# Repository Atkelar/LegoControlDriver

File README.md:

# LegoControlDriver
Lego Control II to Arduino interface code and info.

This is the code related to the video here: https://www.youtube.com/watch?v=ZT2Cm_PV4GQ

There are plenty of comments in the source code, here's a rundown of the projects:

## Lego-Control-II-Driver 
This is the main Arduino Project - i.e. file - for the driver. Single file only so far, but uses the TimerInterrupt library.

## KiCAD
A simple schematic and PCB for interfacing the Arduino pinout with the 20 pin flat cable connector.

## Atkelar.LegoControlII
My C# library to communicate with the Arduino code. Written in .net core 3.1

## Atkelar.LegoPlotter
A C# command line application that wraps the plotter model and can print a simple HPGL file.

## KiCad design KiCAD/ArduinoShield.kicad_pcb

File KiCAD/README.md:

This KiCAD project contains a simple adapter shield PCB.

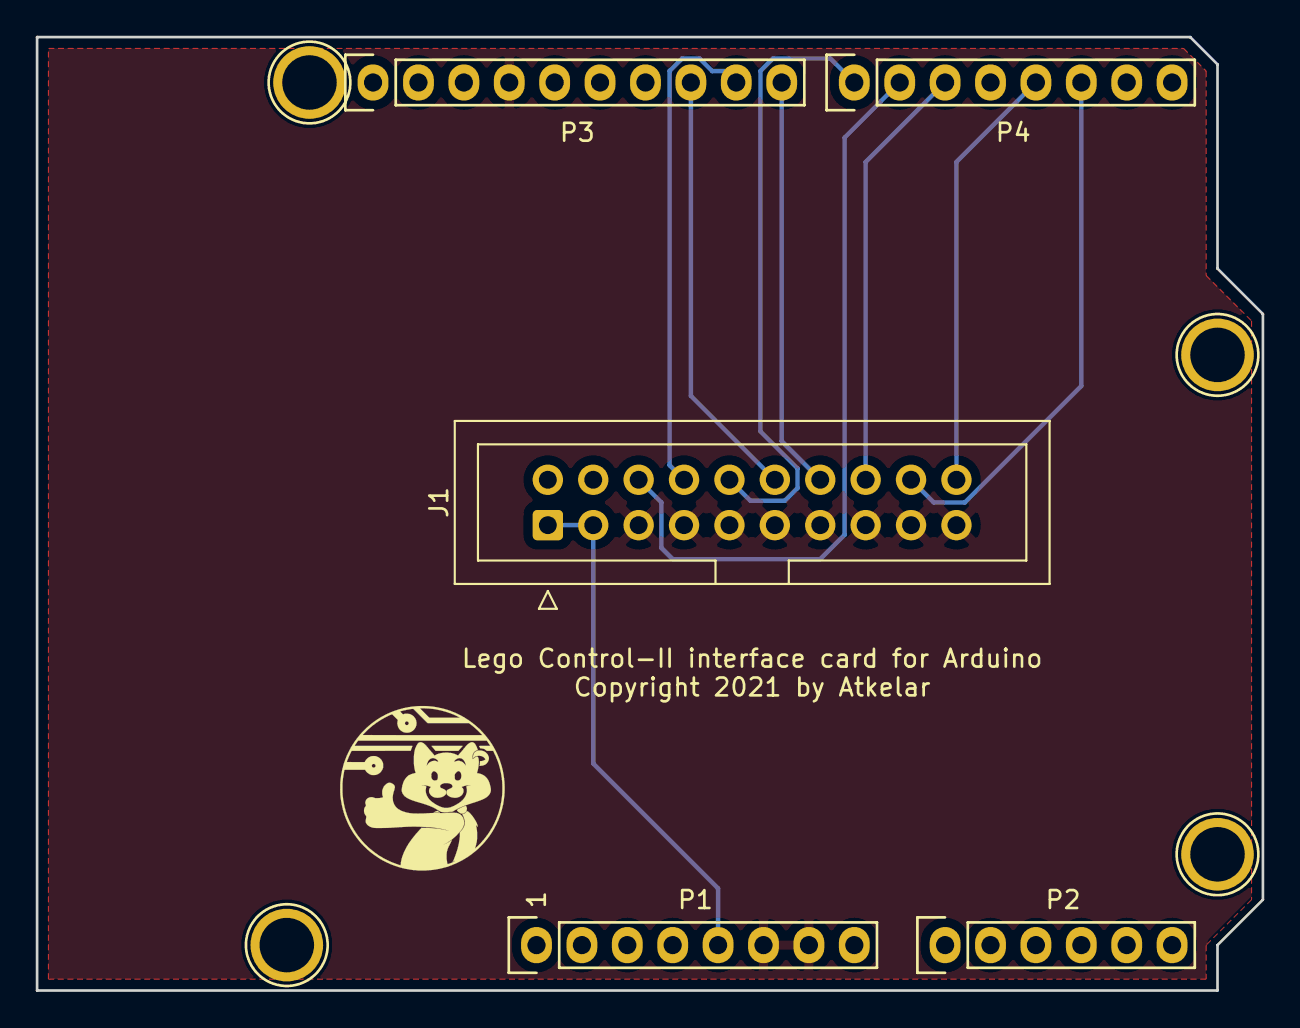
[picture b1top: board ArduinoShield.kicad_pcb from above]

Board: 2 copper layers, 68.6 x 53.3 mm, 9 parts (0 on the bottom side), 12 nets.

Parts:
J1: Control-II; IDC-Header_2x10_P2.54mm_Vertical
P1: Power; Socket_Strip_Arduino_1x08
P2: Analog; Socket_Strip_Arduino_1x06
P3: Digital; Socket_Strip_Arduino_1x10
P4: Digital; Socket_Strip_Arduino_1x08
P5, P6, P7, P8: CONN_01X01; Arduino_1pin

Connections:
+5V: J1.1, J1.3, P1.5
/2: J1.18, P4.6
/3(**): J1.20, P4.5
/5(**): J1.16, P4.3
/6(**): J1.6, P4.2
/7: J1.10, P4.1
/8: J1.14, P3.10
/9(**): J1.8, P3.9
/10(**/SS): J1.12, P3.8
/A4(SDA): P2.5, P3.2
/A5(SCL): P2.6, P3.1
GND: J1.5, J1.7, J1.9, J1.11, J1.13, J1.15, J1.17, J1.19, P1.6, P1.7, P3.4

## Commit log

2021-09-11 Create Lego-Control-II-Driver.ino
    Created Driver Code file.

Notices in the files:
KiCAD/ArduinoShield.kicad_pcb:
Copyright 2021 by Atkelar
